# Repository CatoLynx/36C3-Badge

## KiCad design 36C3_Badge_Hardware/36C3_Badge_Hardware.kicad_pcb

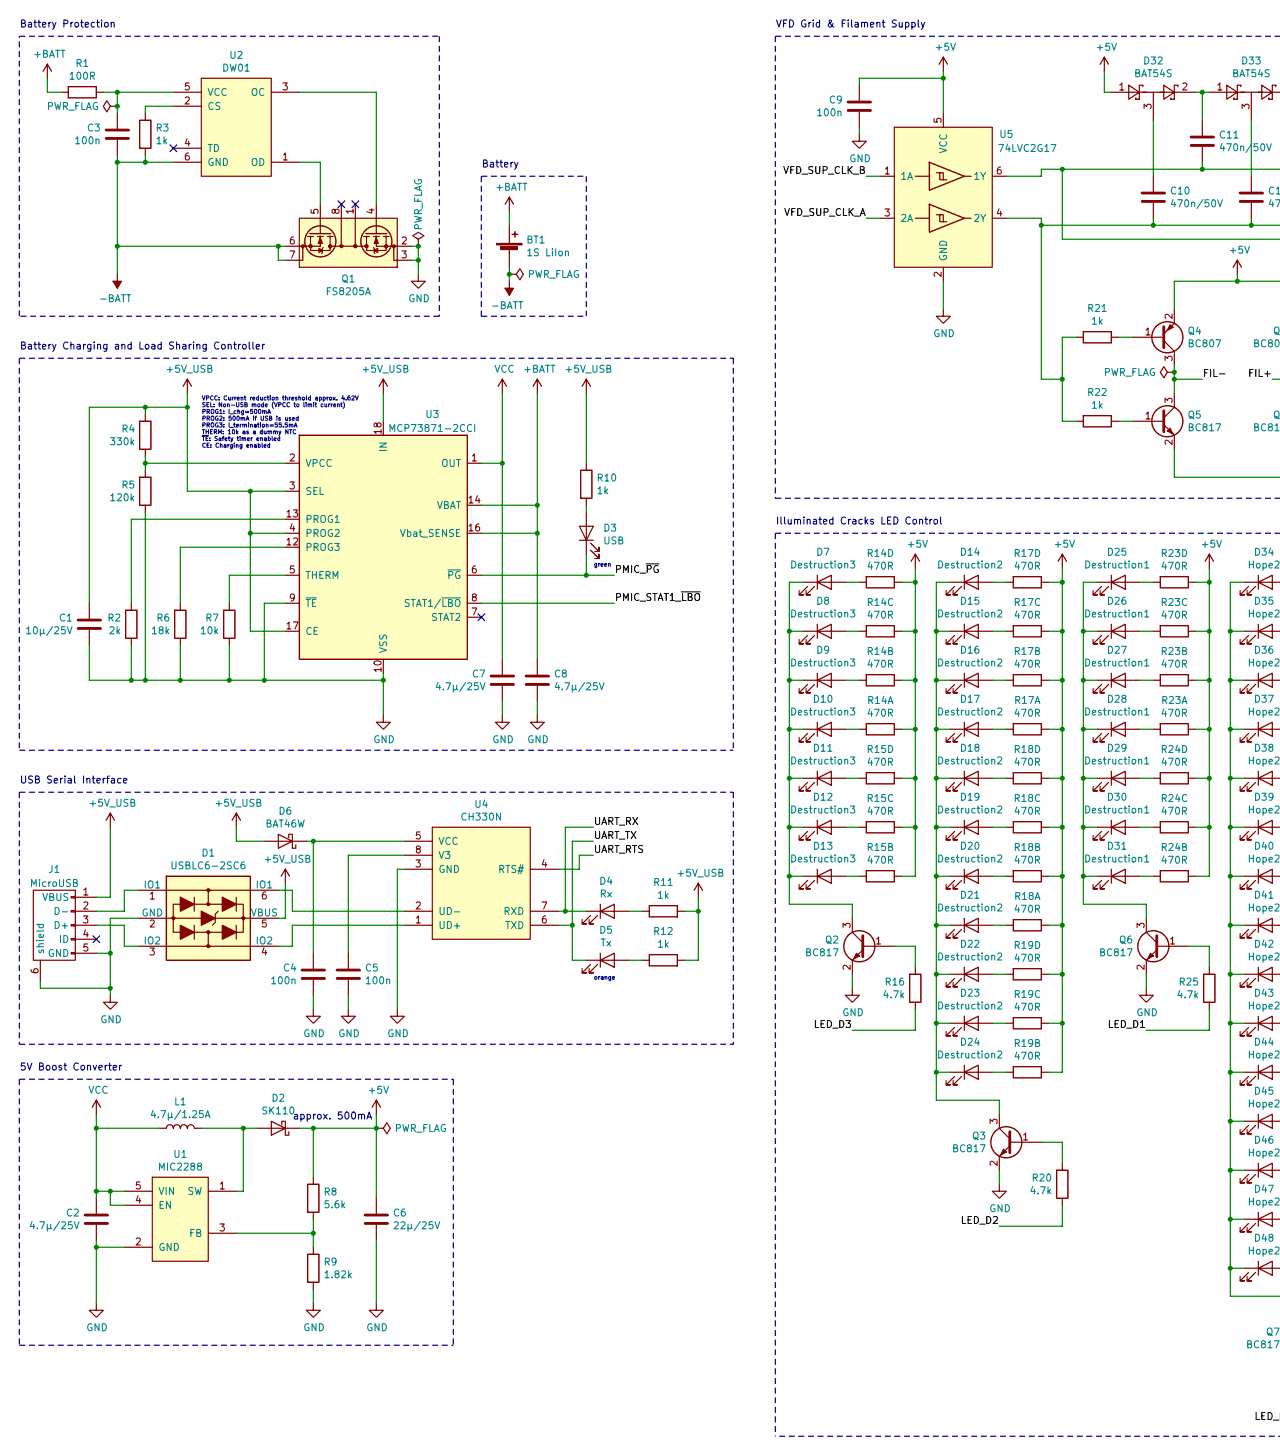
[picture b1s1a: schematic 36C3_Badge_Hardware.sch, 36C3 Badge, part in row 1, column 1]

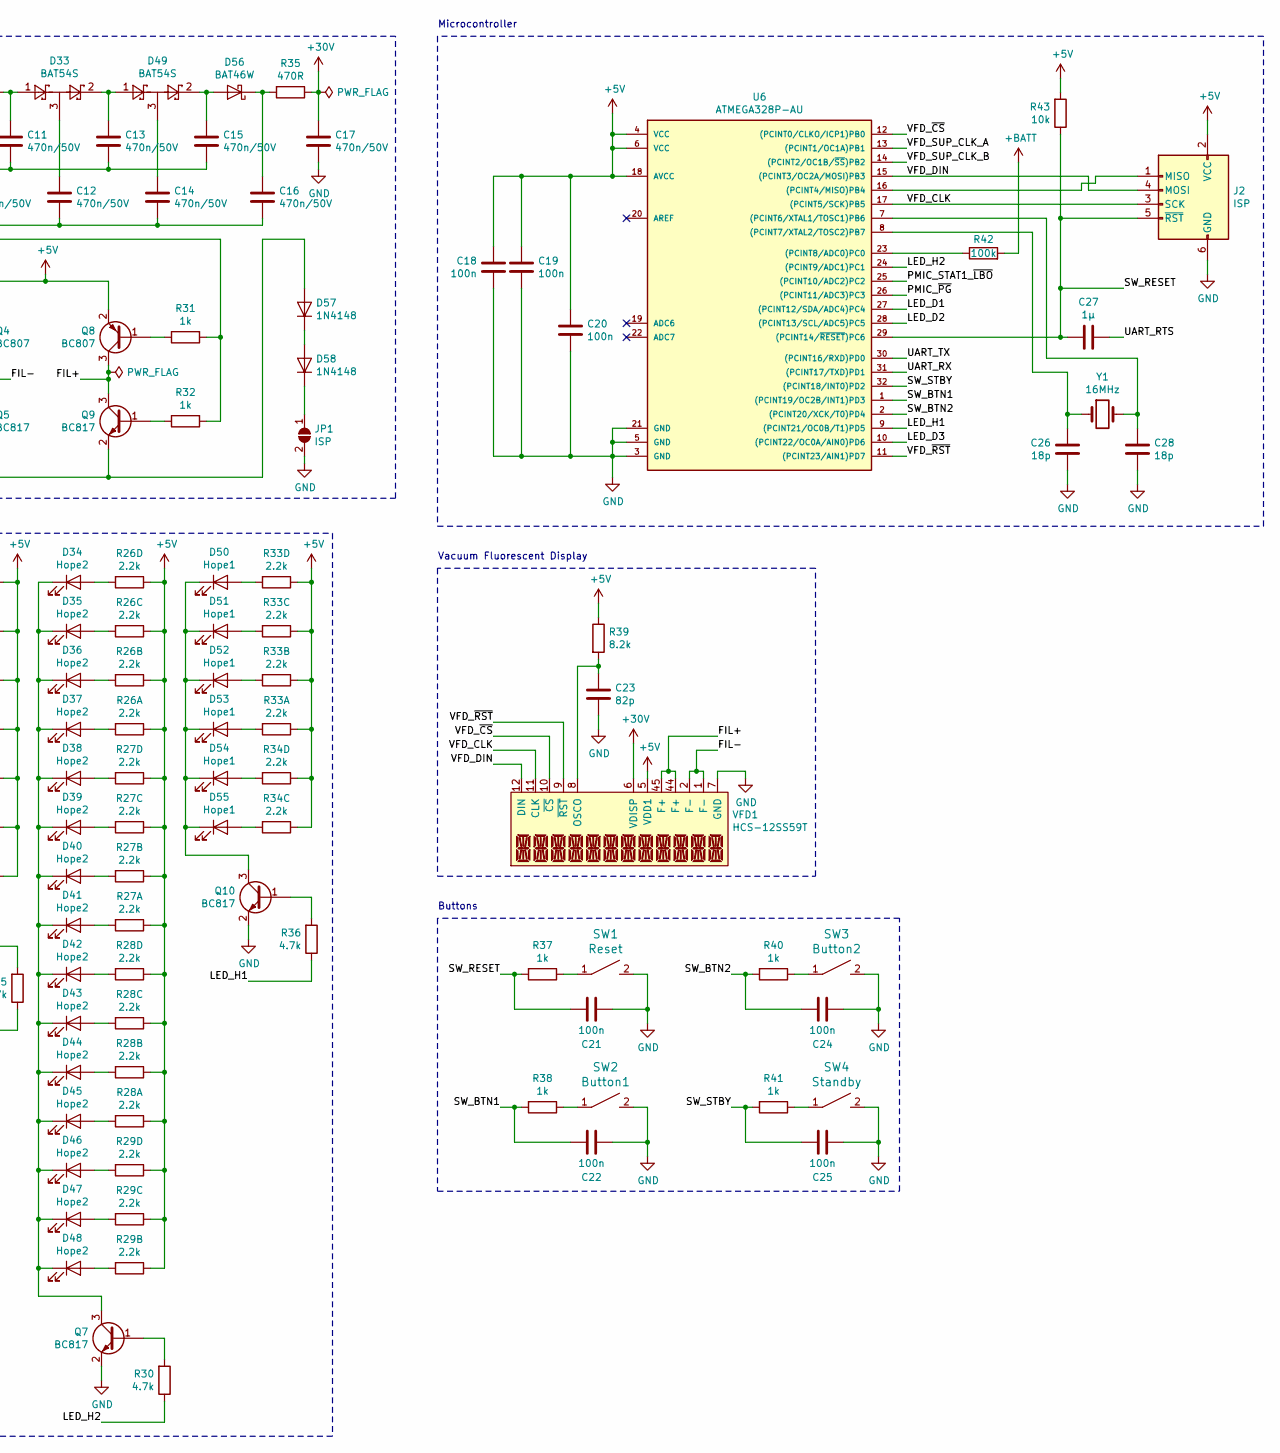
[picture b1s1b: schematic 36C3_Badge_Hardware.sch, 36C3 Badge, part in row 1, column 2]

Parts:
BT1: 1S LiIon; 1S_18650_Holder_with_Spacers
C1: 10µ/25V; C_0805
C2, C7, C8: 4.7µ/25V; C_0805
C3, C4, C5, C9, C18, C19, C20, C21, C22, C24, C25: 100n; C_0603
C6: 22µ/25V; C_0805
C10, C11, C12, C13, C14, C15, C16, C17: 470n/50V; C_0805
C23: 82p; C_0603
C26, C28: 18p; C_0603
C27: 1µ; C_0805
D1: USBLC6-2SC6; SOT-23-6
D2: SK110; D_SMA_Standard
D3: USB; LED_0603
D4: Rx; LED_0603
D5: Tx; LED_0603
D6, D56: BAT46W; D_SOD-123
D7, D8, D9, D10, D11, D12, D13: Destruction3; LED_SideFacing_0802
D14, D15, D16, D17, D18, D19, D20, D21, D22, D23, D24: Destruction2; LED_SideFacing_0802
D25, D26, D27, D28, D29, D30, D31: Destruction1; LED_SideFacing_0802
D32, D33, D49: BAT54S; SOT-23
D34, D35, D36, D37, D38, D39, D40, D41, D42, D43, D44, D45, D46, D47, D48: Hope2; LED_SideFacing_0802
D50, D51, D52, D53, D54, D55: Hope1; LED_SideFacing_0802
D57, D58: 1N4148; D_0603
J1: MicroUSB; MicroUSB_Amphenol_10118192
J2: ISP; Pin_Header_Straight_SMT_02x03
JP1: ISP; Jumper_SolderBridge
L1: 4.7µ/1.25A; Inductor_3x3mm
Q1: FS8205A; TSSOP-8_4.4x3mm_Pitch0.65mm
Q2, Q3, Q5, Q6, Q7, Q9, Q10: BC817; SOT-23
Q4, Q8: BC807; SOT-23
R1: 100R; R_0603
R2: 2k; R_0603
R3, R10, R11, R12, R21, R22, R31, R32, R37, R38, R40, R41: 1k; R_0603
R4: 330k; R_0603
R5: 120k; R_0603
R6: 18k; R_0603
R7, R43: 10k; R_0603
R8: 5.6k; R_0603
R9: 1.82k; R_0603
R14, R15, R17, R18, R19, R23, R24: 470R; R_Array_Concave_4x0603
R16, R20, R25, R30, R36: 4.7k; R_0603
R26, R27, R28, R29, R33, R34: 2.2k; R_Array_Concave_4x0603
R35: 470R; R_0603
R39: 8.2k; R_0603
R42: 100k; R_0603
SW1: Reset; SW_SPST_SKQG
SW2: Button1; SW_SPST_SKQG
SW3: Button2; SW_SPST_SKQG
SW4: Standby; SW_SPST_SKQG
U1: MIC2288; SOT-23-5
U2: DW01; SOT-23-6
U3: MCP73871-2CCI; QFN-20-1EP_4x4mm_Pitch0.5mm
U4: CH330N; SOIC-8_3.9x4.9mm_Pitch1.27mm
U5: 74LVC2G17; SOT-457
U6: ATMEGA328P-AU; TQFP-32_7x7mm_Pitch0.8mm
VFD1: HCS-12SS59T; VFD_HCS-12SS59T_noSilk
Y1: 16MHz; Crystal_HC49-SD_SMD

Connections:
+5V: C6.1, C9.2, C18.2, C19.1, C20.1, D2.1 (K), D32.1, J2.2 (VCC), Q4.2 (E), Q8.2 (E), R8.1, R14.1, R14.2, R14.3, R14.4, R15.2, R15.3, R15.4, R17.1, R17.2, R17.3, R17.4, R18.1, R18.2, R18.3, R18.4, R19.2, R19.3, R19.4, R23.1, R23.2, R23.3, R23.4, R24.2, R24.3, R24.4, R26.1, R26.2, R26.3, R26.4, R27.1, R27.2, R27.3, R27.4, R28.1, R28.2, R28.3, R28.4, R29.2, R29.3, R29.4, R33.1, R33.2, R33.3, R33.4, R34.3, R34.4, R39.1, R43.2, U5.5 (VCC), U6.4 (VCC), U6.6 (VCC), U6.18 (AVCC), VFD1.5 (VDD1)
+5V_USB: C1.2, D1.5 (VBUS), D6.2 (A), J1.1 (VBUS), R4.2, R10.1, R11.2, R12.2, U3.3 (SEL), U3.4 (PROG2), U3.17 (CE), U3.18 (IN), U3.19 (IN)
+30V: C17.1, R35.1, VFD1.6 (VDISP)
+BATT: BT1.1 (+), C8.1, R1.2, R42.2, U3.14 (VBAT), U3.15 (VBAT), U3.16 (Vbat_SENSE)
-BATT: BT1.2 (-), C3.1, Q1.6 (S2), Q1.7 (S2), R3.2, U2.6 (GND)
/FIL+: Q8.3 (C), Q9.3 (C), VFD1.44 (F+), VFD1.45 (F+)
/FIL-: Q4.3 (C), Q5.3 (C), VFD1.1 (F-), VFD1.2 (F-)
/LED_D1: R25.1, U6.27 ((PCINT12/SDA/ADC4)PC4)
/LED_D2: R20.1, U6.28 ((PCINT13/SCL/ADC5)PC5)
/LED_D3: R16.1, U6.10 ((PCINT22/OC0A/AIN0)PD6)
/LED_H1: R36.1, U6.9 ((PCINT21/OC0B/T1)PD5)
/LED_H2: R30.1, U6.24 ((PCINT9/ADC1)PC1)
/PMIC_STAT1_~LBO: U3.8 (STAT1/~LBO~), U6.25 ((PCINT10/ADC2)PC2)
/PMIC_~PG: D3.1 (K), U3.6 (~PG~), U6.26 ((PCINT11/ADC3)PC3)
/SW_BTN1: C22.1, R38.2, U6.1 ((PCINT19/OC2B/INT1)PD3)
/SW_BTN2: C24.1, R40.2, U6.2 ((PCINT20/XCK/T0)PD4)
/SW_RESET: C21.1, C27.2, J2.5 (~RST), R37.2, R43.1, U6.29 ((PCINT14/~RESET~)PC6)
/SW_STBY: C25.1, R41.2, U6.32 ((PCINT18/INT0)PD2)
/UART_RTS: C27.1, U4.4 (RTS#)
/UART_RX: D4.1 (K), U4.7 (RXD), U6.31 ((PCINT17/TXD)PD1)
/UART_TX: D5.1 (K), U4.6 (TXD), U6.30 ((PCINT16/RXD)PD0)
/VFD_CLK: J2.3 (SCK), U6.17 ((PCINT5/SCK)PB5), VFD1.11 (CLK)
/VFD_DIN: J2.4 (MOSI), U6.15 ((PCINT3/OC2A/MOSI)PB3), VFD1.12 (DIN)
/VFD_SUP_CLK_A: U5.3 (2A), U6.13 ((PCINT1/OC1A)PB1)
/VFD_SUP_CLK_B: U5.1 (1A), U6.14 ((PCINT2/OC1B/~SS~)PB2)
/VFD_~CS: U6.12 ((PCINT0/CLKO/ICP1)PB0), VFD1.10 (~CS)
/VFD_~RST: U6.11 ((PCINT23/AIN1)PD7), VFD1.9 (~RST)
GND: C1.1, C2.1, C4.1, C5.2, C6.2, C7.1, C8.2, C9.1, C17.2, C18.1, C19.2, C20.2, C21.2, C22.2, C23.2, C24.2, C25.2, C26.1, C28.2, D1.2 (GND), J1.5 (GND), J1.6 (shield), J2.6 (GND), JP1.2 (B), Q1.2 (S1), Q1.3 (S1), Q2.2 (E), Q3.2 (E), Q6.2 (E), Q7.2 (E), Q10.2 (E), R2.1, R5.1, R6.1, R7.1, R9.2, SW1.2, SW2.2, SW3.2, SW4.2, U1.2 (GND), U3.9 (~TE), U3.10 (VSS), U3.11 (VSS), U3.21 (VSS), U4.3 (GND), U5.2 (GND), U6.3 (GND), U6.5 (GND), U6.21 (GND), VFD1.7 (GND)
unnamed: C3.2, R1.1, U2.5 (VCC)
unnamed: C4.2, D6.1 (K), U4.5 (VCC)
unnamed: C5.1, U4.8 (V3)
unnamed: C10.1, D32.3
unnamed: C10.2, C12.2, C14.2, C16.2, R21.2, R22.2, U5.4 (2Y)
unnamed: C11.1, D32.2, D33.1
unnamed: C11.2, C13.2, C15.2, R31.2, R32.2, U5.6 (1Y)
unnamed: C12.1, D33.3
unnamed: C13.1, D33.2, D49.1
unnamed: C14.1, D49.3
unnamed: C15.1, D49.2, D56.2 (A)
unnamed: C16.1, D56.1 (K), R35.2
unnamed: C23.1, R39.2, VFD1.8 (OSCO)
unnamed: C26.2, U6.8 ((PCINT7/XTAL2/TOSC2)PB7), Y1.1
unnamed: C28.1, U6.7 ((PCINT6/XTAL1/TOSC1)PB6), Y1.2
unnamed: D1.1 (IO1), J1.2 (D-)
unnamed: D1.3 (IO2), J1.3 (D+)
unnamed: D1.4 (IO2), U4.1 (UD+)
unnamed: D1.6 (IO1), U4.2 (UD-)
unnamed: D2.2 (A), L1.2, U1.1 (SW)
unnamed: D3.2 (A), R10.2
unnamed: D4.2 (A), R11.1
unnamed: D5.2 (A), R12.1
unnamed: D7.2 (A), R14.5
unnamed: D8.2 (A), R14.6
unnamed: D9.2 (A), R14.7
unnamed: D7.1 (K), D8.1 (K), D9.1 (K), D10.1 (K), D11.1 (K), D12.1 (K), D13.1 (K), Q2.3 (C)
unnamed: D10.2 (A), R14.8
unnamed: D11.2 (A), R15.5
unnamed: D12.2 (A), R15.6
unnamed: D13.2 (A), R15.7
unnamed: D14.1 (K), D15.1 (K), D16.1 (K), D17.1 (K), D18.1 (K), D19.1 (K), D20.1 (K), D21.1 (K), D22.1 (K), D23.1 (K), D24.1 (K), Q3.3 (C)
unnamed: D14.2 (A), R17.5
unnamed: D15.2 (A), R17.6
unnamed: D16.2 (A), R17.7
unnamed: D17.2 (A), R17.8
unnamed: D18.2 (A), R18.5
unnamed: D19.2 (A), R18.6
unnamed: D20.2 (A), R18.7
unnamed: D21.2 (A), R18.8
unnamed: D22.2 (A), R19.5
unnamed: D23.2 (A), R19.6
unnamed: D24.2 (A), R19.7
unnamed: D25.1 (K), D26.1 (K), D27.1 (K), D28.1 (K), D29.1 (K), D30.1 (K), D31.1 (K), Q6.3 (C)
unnamed: D25.2 (A), R23.5
unnamed: D26.2 (A), R23.6
unnamed: D27.2 (A), R23.7
unnamed: D28.2 (A), R23.8
unnamed: D29.2 (A), R24.5
unnamed: D30.2 (A), R24.6
unnamed: D31.2 (A), R24.7
unnamed: D34.1 (K), D35.1 (K), D36.1 (K), D37.1 (K), D38.1 (K), D39.1 (K), D40.1 (K), D41.1 (K), D42.1 (K), D43.1 (K), D44.1 (K), D45.1 (K), D46.1 (K), D47.1 (K), D48.1 (K), Q7.3 (C)
unnamed: D34.2 (A), R26.5
unnamed: D35.2 (A), R26.6
unnamed: D36.2 (A), R26.7
unnamed: D37.2 (A), R26.8
unnamed: D38.2 (A), R27.5
unnamed: D39.2 (A), R27.6
unnamed: D40.2 (A), R27.7
unnamed: D41.2 (A), R27.8
unnamed: D42.2 (A), R28.5
unnamed: D43.2 (A), R28.6
unnamed: D44.2 (A), R28.7
unnamed: D45.2 (A), R28.8
unnamed: D46.2 (A), R29.5
unnamed: D47.2 (A), R29.6
unnamed: D48.2 (A), R29.7
unnamed: D50.1 (K), D51.1 (K), D52.1 (K), D53.1 (K), D54.1 (K), D55.1 (K), Q10.3 (C)
unnamed: D50.2 (A), R33.5
unnamed: D51.2 (A), R33.6
unnamed: D52.2 (A), R33.7
unnamed: D53.2 (A), R33.8
unnamed: D54.2 (A), R34.5
unnamed: D55.2 (A), R34.6
unnamed: D57.1 (K), D58.2 (A)
unnamed: D57.2 (A), Q5.2 (E), Q9.2 (E)
unnamed: D58.1 (K), JP1.1 (A)
unnamed: J2.1 (MISO), U6.16 ((PCINT4/MISO)PB4)
unnamed: Q1.4 (G1), U2.3 (OC)
unnamed: Q1.5 (G2), U2.1 (OD)
unnamed: Q2.1 (B), R16.2
unnamed: Q3.1 (B), R20.2
unnamed: Q4.1 (B), R21.1
unnamed: Q5.1 (B), R22.1
unnamed: Q6.1 (B), R25.2
unnamed: Q7.1 (B), R30.2
unnamed: Q8.1 (B), R31.1
unnamed: Q9.1 (B), R32.1
unnamed: Q10.1 (B), R36.2
unnamed: R2.2, U3.13 (PROG1)
unnamed: R3.1, U2.2 (CS)
unnamed: R4.1, R5.2, U3.2 (VPCC)
unnamed: R6.2, U3.12 (PROG3)
unnamed: R7.2, U3.5 (THERM)
unnamed: R8.2, R9.1, U1.3 (FB)
unnamed: R37.1, SW1.1
unnamed: R38.1, SW2.1
unnamed: R40.1, SW3.1
unnamed: R41.1, SW4.1
unnamed: R42.1, U6.23 ((PCINT8/ADC0)PC0)
VCC: C2.2, C7.2, L1.1, U1.4 (EN), U1.5 (VIN), U3.1 (OUT), U3.20 (OUT)

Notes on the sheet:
Battery Protection
Battery
orange
USB Serial Interface
approx. 500mA
5V Boost Converter
VFD Grid & Filament Supply
Illuminated Cracks LED Control
Vacuum Fluorescent Display
VPCC: Current reduction threshold approx. 4.62V SEL: Non-USB mode (VPCC to limit current) PROG1: I_chg=500mA PROG2: 500mA if USB is used PROG3: I_termination=55.5mA THERM: 10k as a dummy NTC ~TE~: Safety timer enabled CE: Charging enabled
Battery Charging and Load Sharing Controller
green
Buttons
Microcontroller

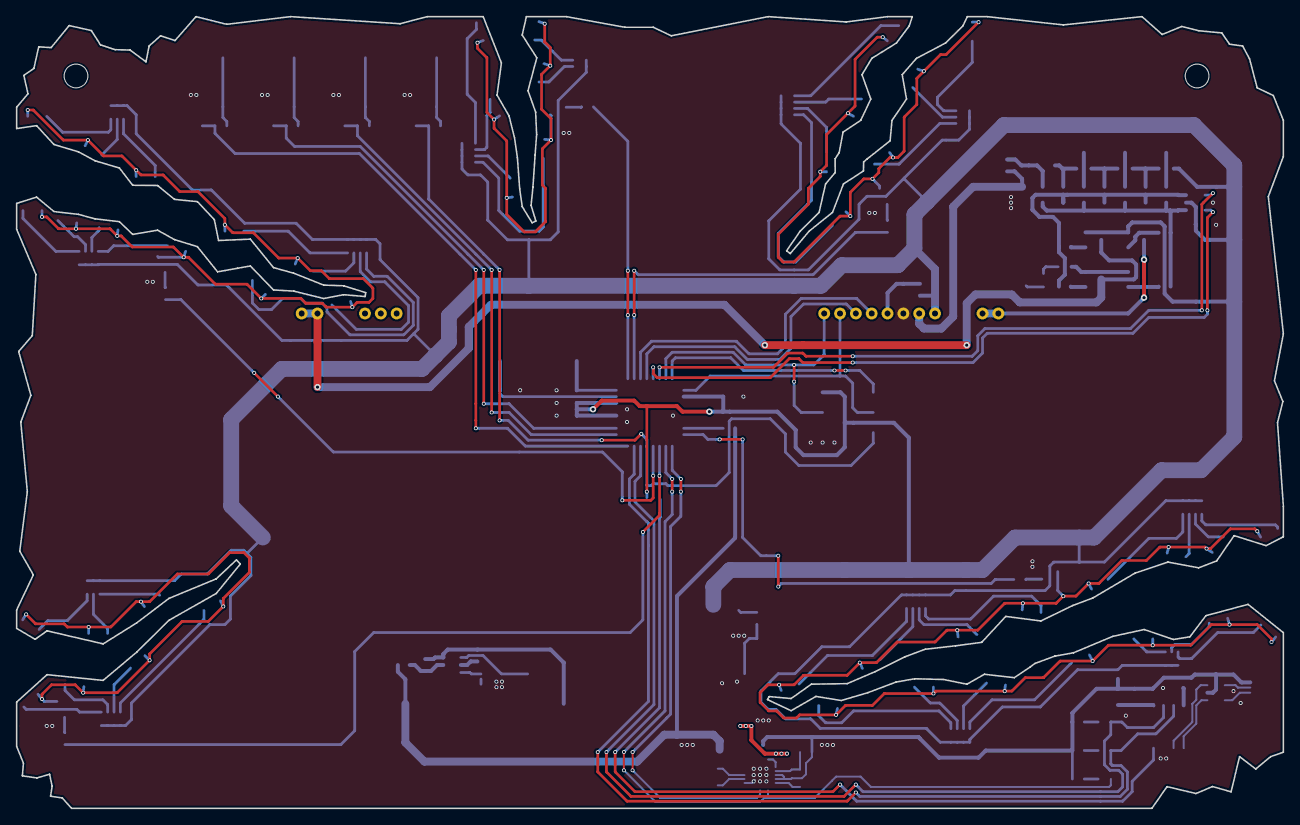
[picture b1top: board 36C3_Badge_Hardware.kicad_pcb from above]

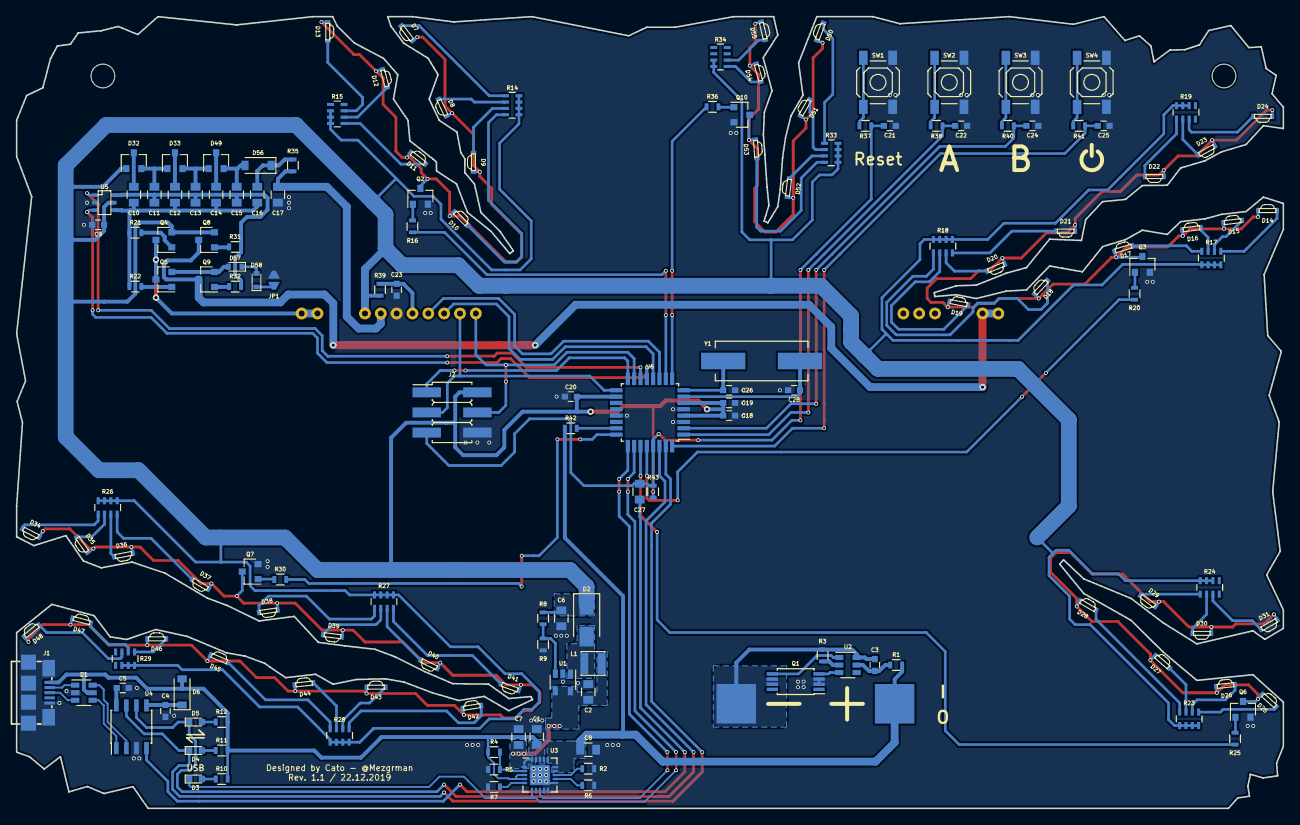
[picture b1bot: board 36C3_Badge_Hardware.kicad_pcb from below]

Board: 2 copper layers, 160.0 x 100.0 mm, 155 parts (154 on the bottom side), 129 nets.

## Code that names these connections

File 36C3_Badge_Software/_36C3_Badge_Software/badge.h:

#pragma once

#include <SPI.h>

#define VCC_VOLTAGE   5060  // Calibration value (actual value of 5V rail in mV)

#define SPI_PARAMS    2000000, LSBFIRST, SPI_MODE3
#define SUPPLY_CLK    62    // Clocked VFD anode & filament supply, ~16 kHz

#define VFD_DCRAM_WR  0x10  // ccccaaaa dddddddd dddddddd ..
#define VFD_CGRAM_WR  0x20  // ccccaaaa dddddddd dddddddd ..
#define VFD_ADRAM_WR  0x30  // ccccaaaa ******dd ******dd ..
#define VFD_DUTY      0x50  // ccccdddd
#define VFD_NUMDIGIT  0x60  // ccccdddd
#define VFD_LIGHTS    0x70  // cccc**dd

#define VFD_LI_NORM   0x00  // Normal operation
#define VFD_LI_OFF    0x01  // All segments off
#define VFD_LI_ON     0x02  // All segments on

#define VFD_NUM_CHARS 12    // Number of characters on VFD
#define VFD_BUF_SIZE  50   // Scroll buffer for VFD

#define VFD_ANI_DELAY 15    // Animation frame delay in milliseconds

typedef enum Crack {
  DESTRUCTION1,
  DESTRUCTION2,
  DESTRUCTION3,
  HOPE1,
  HOPE2
} crack_t;

typedef enum VFDTestMode {
  NONE,
  ALL_ON,
  ALL_OFF
} vfd_test_mode_t;

typedef enum Buttons {
  SW_NONE = 0,
  SW_STBY = 1,
  SW_A = 2,
  SW_B = 4
} buttons_t;

typedef enum VFDAnimations {
  ANIMATION_NONE,
  ANIMATION_RANDOM,
  ANIMATION_FLIP,
  ANIMATION_SLIDE,
  ANIMATION_FADE
} vfd_animation_t;

class Badge
{
  public:
    static const int PIN_VFD_RST = 7;  // active low
    static const int PIN_VFD_CS = 8;   // active low
    static const int PIN_VFD_SUP_CLK_A = 9;
    static const int PIN_VFD_SUP_CLK_B = 10;
    static const int PIN_LED_D1 = 18;
    static const int PIN_LED_D2 = 19;
    static const int PIN_LED_D3 = 6;
    static const int PIN_LED_H1 = 5;
    static const int PIN_LED_H2 = 15;
    static const int PIN_BATT_ADC = A0;
    static const int PIN_SW_STBY = 2;
    static const int PIN_SW_A = 3;
    static const int PIN_SW_B = 4;
    static const int PIN_PMIC_STAT1_LBO = 16; // LBO active low
    static const int PIN_PMIC_PG = 17;  // active low

    volatile uint8_t pwmCounter = 0;
    volatile uint16_t timer2InterruptCounter = 0;
    volatile uint8_t vfdAnimInterruptCounter = 0;
    uint8_t pwmValueDestruction1 = 0;
    uint8_t pwmValueDestruction2 = 0;
    uint8_t pwmValueDestruction3 = 0;
    uint8_t pwmValueHope1 = 0;
    uint8_t pwmValueHope2 = 0;

    volatile uint8_t vfdAnimActive = 0;

    Badge();
    void begin();
    void wakeUp();
    void sleep();
    void vfdSetBrightness(uint8_t level);
    void vfdSetSupply(uint8_t state);
    void vfdSetTestMode(vfd_test_mode_t mode);
    void vfdWriteText(char* text);
    void vfdAnimate(char *text, vfd_animation_t animation);
    void vfdStopAnimation();
    void vfdSetCharacter(uint8_t addr, char* charData);
    char vfdGetCode(char c);
    void vfdSetScrollSpeed(uint32_t speed);
    void vfdUpdateScroll();
    void vfdUpdateAnimation();
    void setCrack(crack_t crack, uint8_t value);
    void battUpdateAverage();
    uint16_t battGetVoltage();
    uint8_t battGetLevel();
    buttons_t btnGetAll();
    uint8_t pwrGetUSB();
    uint8_t pwrGetCharging();
    uint8_t pwrGetLowBatt();
    void pwrCheckError();

  protected:

  private:
    char vfdBuffer[VFD_BUF_SIZE];
    volatile char vfdAnimBuffer[VFD_NUM_CHARS + 1];
    const SPISettings spiConfig;

    volatile int16_t vfdScrollLen;
    volatile int16_t vfdScrollPos;
    volatile uint32_t vfdScrollSpeed;

    volatile uint16_t vfdSetScrollSpeedTickCount = 0;

    volatile uint8_t vfdBrightness = 15;
    volatile vfd_animation_t vfdAnimMode = ANIMATION_NONE;
    volatile char vfdAnimTarget[VFD_BUF_SIZE];
    volatile uint8_t vfdAnimFrame = 0;
    volatile uint8_t vfdAnimBrightness = vfdBrightness;

    static const uint8_t BATT_AVG_NUM_VALUES = 10;
    volatile uint16_t battAverage = 0;
    volatile uint32_t battAvgSum = 0;
    volatile uint16_t battAvgPos = 0;
    volatile uint16_t battAvgValues[BATT_AVG_NUM_VALUES] = {0};

    void vfdReset();
    void vfdSendCmd(char cmd, char arg);
    void vfdSendCmdSeq(char cmd, char arg);
    void vfdSendChar(char c);
    void vfdWriteTextInternal(char* text);
    void vfdUpdate();
    void vfdSPIBegin();
    void vfdSPIEnd();
    void vfdSPISelect();
    void vfdSPIDeselect();
    void vfdClearBuffer();
    void startTimer2();
    void stopTimer2();
};

extern Badge badge;

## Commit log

2019-12-06 Initial commit, schematic (hopefully) complete
2019-12-06 Removed power switch, added footprints
2019-12-06 Rotated pinouts of Q1 and resistor arrays 180° for easier routing
2019-12-06 Removed D6 (Power LED) since the switch is now gone too
2019-12-06 Fixed incorrect input net to boost converter (was +BATT instead of VCC)
2019-12-06 Fixed EN of boost converter not being tied to VIN
2019-12-07 Fixed missing +5V connection to VFD filament H-bridge
2019-12-07 Updated schematic pdf
2019-12-08 Swapped some pins on the microcontroller for easier routing
2019-12-08 Changed VFD footprint to have no silkscreen
2019-12-08 First revision of PCB
2019-12-08 Added 3D renders
2019-12-08 Removed unnecessary xml file
2019-12-08 Added readme
2019-12-15 First rough version of software (just a demo)
2019-12-15 Added CAD files
2019-12-16 Tidied up code, implemented 6 bit software PWM for the illuminated cracks
2019-12-17 Added custom char generation and battery readout
2019-12-17 Added button input and sleep mode
2019-12-17 Added functions for querying power status
2019-12-17 Added charging breathing animation
2019-12-22 Schematic / Board updates and bugfixes:
    - Updated crack LED resistor values after testing
    - Changed microcontroller reset capacitor from 100nF to 1µF and case from 0603 to 0805
    - Changed MMBTA type transistors to BC types (MMBTA didn't work in the VFD filament H-Bridge)
    - Added Schottky diode in series to CH330 VCC pin. This fixes an error where the badge would erroneously detect USB power when the CH330 was backfed via the high Tx pin.
2019-12-22 Updated Hope2 crack insert
2019-12-22 Test code using MD_Menu library
2019-12-22 Added VFD animation code to badge library
2019-12-23 Multiple changes:
    - Added configurable and selectable text animation setups (defined in config.h)
    - Changed VFD scroll interval from 100 to 10 ms
    - Added function to get battery level in percent (assuming cutoff at 3.0V)
2019-12-23 VFD animations now timer-based, added new options to VFD text list
2019-12-23 Added photo
2019-12-23 Added BOM
2019-12-23 Added GPLv3 license
2019-12-29 Added power error check to detect a not-yet-known design error
2021-09-15 Commit open changes (debounce, progmem)
